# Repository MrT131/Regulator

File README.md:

# Regulator
# Was designed using KiCad 5.1.0

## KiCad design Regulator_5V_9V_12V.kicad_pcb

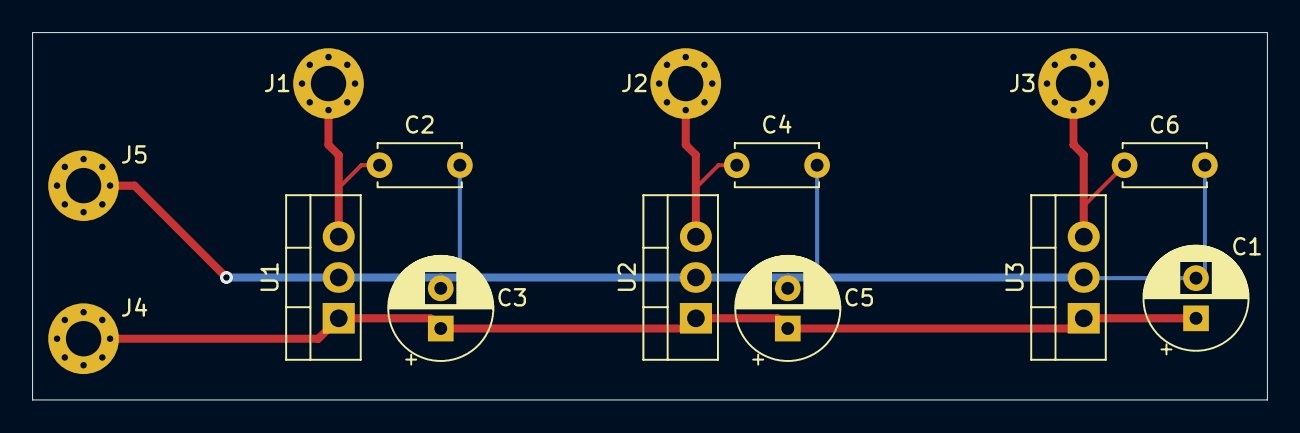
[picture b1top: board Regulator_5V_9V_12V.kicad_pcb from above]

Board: 2 copper layers, 76.8 x 22.9 mm, 14 parts (0 on the bottom side), 5 nets.

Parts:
C1, C3, C5: 0.33uF; CP_Radial_D6.3mm_P2.50mm
C2, C4, C6: 1uF; C_Disc_D5.0mm_W2.5mm_P5.00mm
J1: Output 1; MountingHole_2.2mm_M2_Pad_Via
J2: Output 2; MountingHole_2.2mm_M2_Pad_Via
J3: Output 3; MountingHole_2.2mm_M2_Pad_Via
J4: Input; MountingHole_2.2mm_M2_Pad_Via
J5: GND; MountingHole_2.2mm_M2_Pad_Via
U1: L7805; TO-220-3_Vertical
U2: L7809; TO-220-3_Vertical
U3: L7812; TO-220-3_Vertical

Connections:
unnamed: C1.1, C3.1, C5.1, J4.1, U1.1, U2.1, U3.1
unnamed: C1.2, C2.2, C3.2, C4.2, C5.2, C6.2, J5.1, U1.2, U2.2, U3.2
unnamed: C2.1, J1.1, U1.3
unnamed: C4.1, J2.1, U2.3
unnamed: C6.1, J3.1, U3.3

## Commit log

2019-05-06 Create first file
